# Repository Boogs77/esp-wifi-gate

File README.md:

# esp-wifi-gate
ESP circuit for Wifi Came gate control

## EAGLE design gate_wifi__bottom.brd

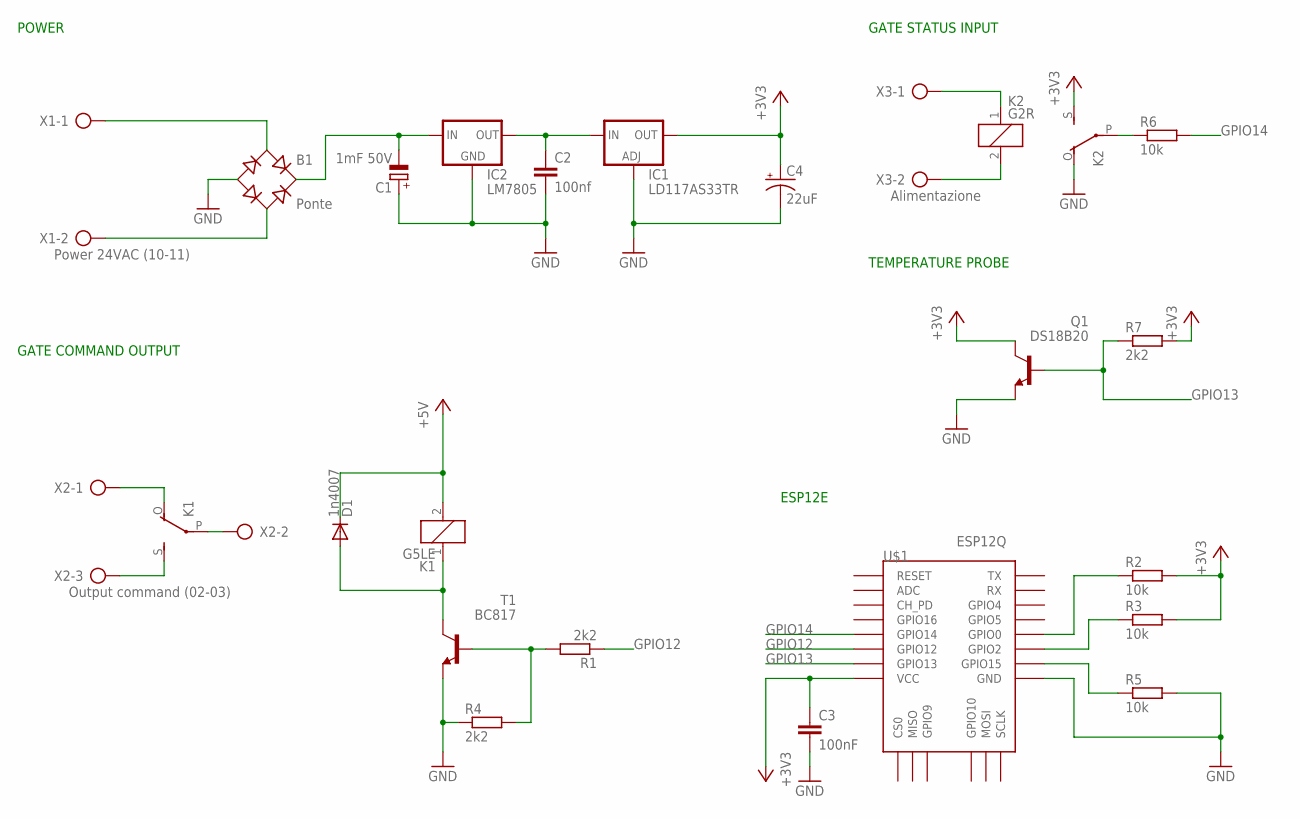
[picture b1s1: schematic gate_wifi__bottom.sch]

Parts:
B1: Ponte; RB1A_MOD
C1: 1mF 50V; E5-8,5
C2: 100nf; C0805K
C3: 100nF; C0805K
C4: 22uF; E2,5-5
D1: 1n4007; DO-214AC
IC1: LD117AS33TR; SOT223
IC2: LM7805; 78XXS
K1: G5LE
K2: G2R
Q1: DS18B20; TO92
R1, R4, R7: 2k2; M0805
R2, R3, R5, R6: 10k; M0805
T1: BC817; SOT23-BEC
U$1: ESP12Q
X1: Power 24VAC (10-11); AK500/2
X2: Output command (02-03); AK500/3
X3: Alimentazione; AK500/2

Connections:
+3V3: C3.1, C4.+, IC1.4 (OUT), K2.S, Q1.1 (C), R2.2, R3.2, R7.2, U$1.VCC
+5V: D1.C, K1.2
GND: B1.-, C1.+, C2.2, C3.2, C4.-, IC1.1 (ADJ), IC2.GND, K2.O, Q1.3 (E), R4.1, R5.2, T1.E, U$1.GND
GPIO12: R1.1, U$1.GPIO12
GPIO13: Q1.2 (B), R7.1, U$1.GPIO13
GPIO14: R6.2, U$1.GPIO14
unnamed: B1.AC1, X1.1
unnamed: B1.AC2, X1.2
unnamed: K1.P, X2.2
unnamed: K1.S, X2.3
unnamed: K1.O, X2.1
unnamed: D1.A, K1.1, T1.C
unnamed: R5.1, U$1.GPIO15
unnamed: R1.2, R4.2, T1.B
unnamed: B1.+, C1.-, IC2.IN
unnamed: K2.1, X3.1
unnamed: C2.1, IC1.3 (IN), IC2.OUT
unnamed: K2.2, X3.2
unnamed: R3.1, U$1.GPIO2
unnamed: R2.1, U$1.GPIO0
unnamed: K2.P, R6.1

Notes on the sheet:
POWER
GATE COMMAND OUTPUT
GATE STATUS INPUT
TEMPERATURE PROBE
ESP12E

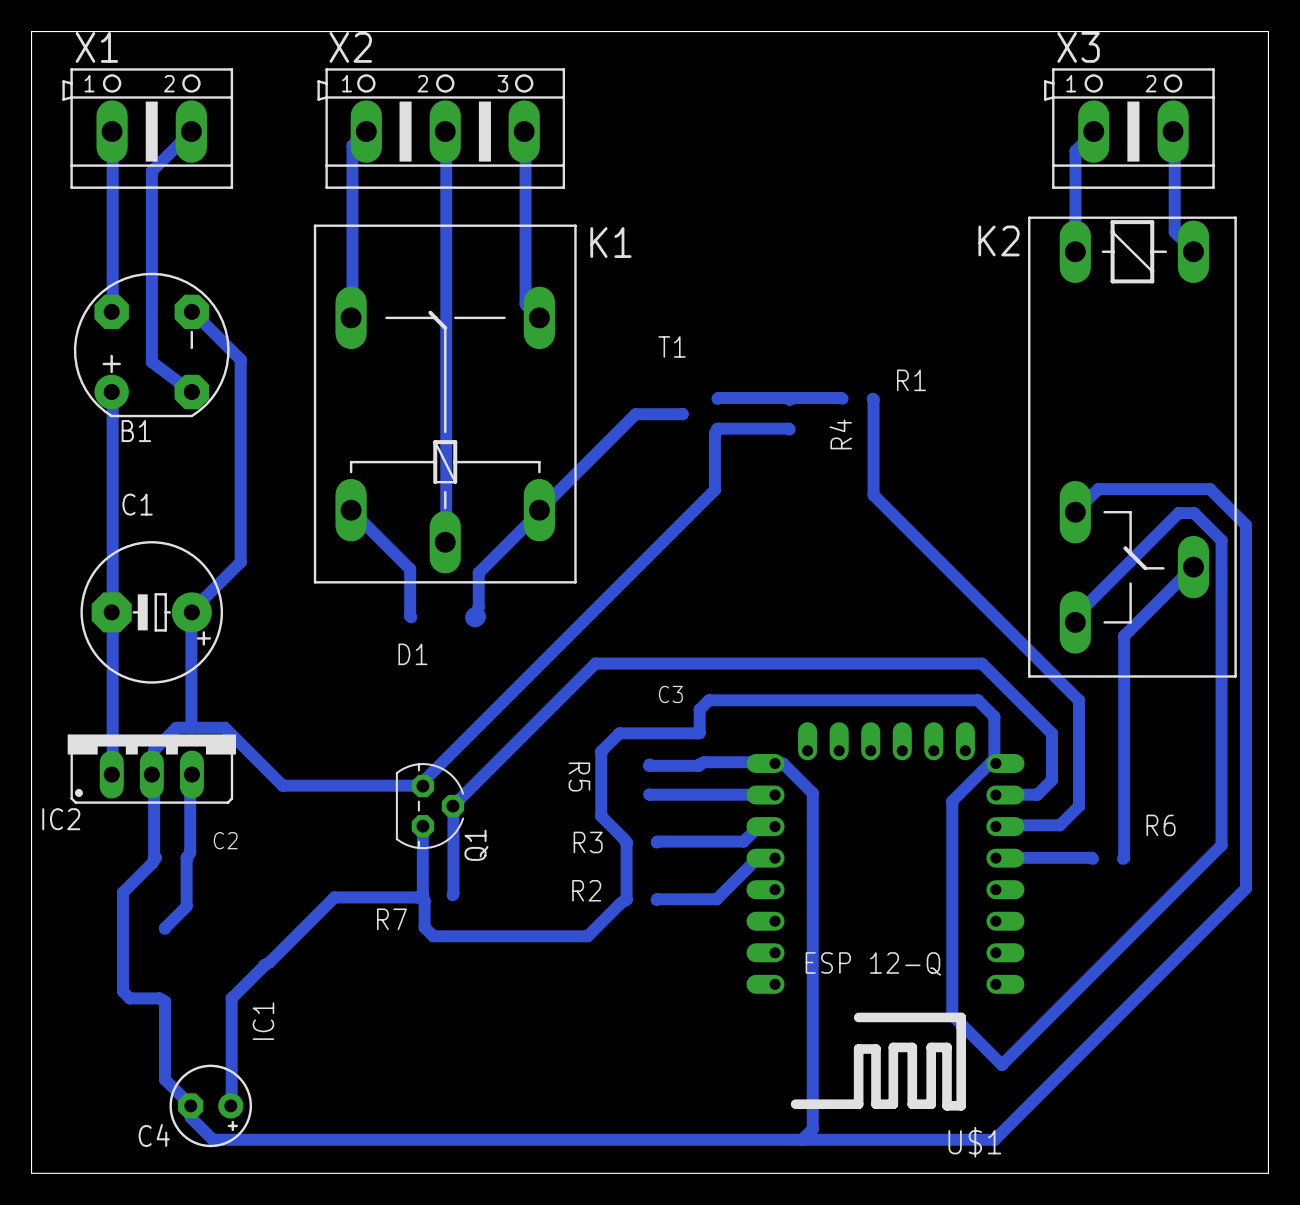
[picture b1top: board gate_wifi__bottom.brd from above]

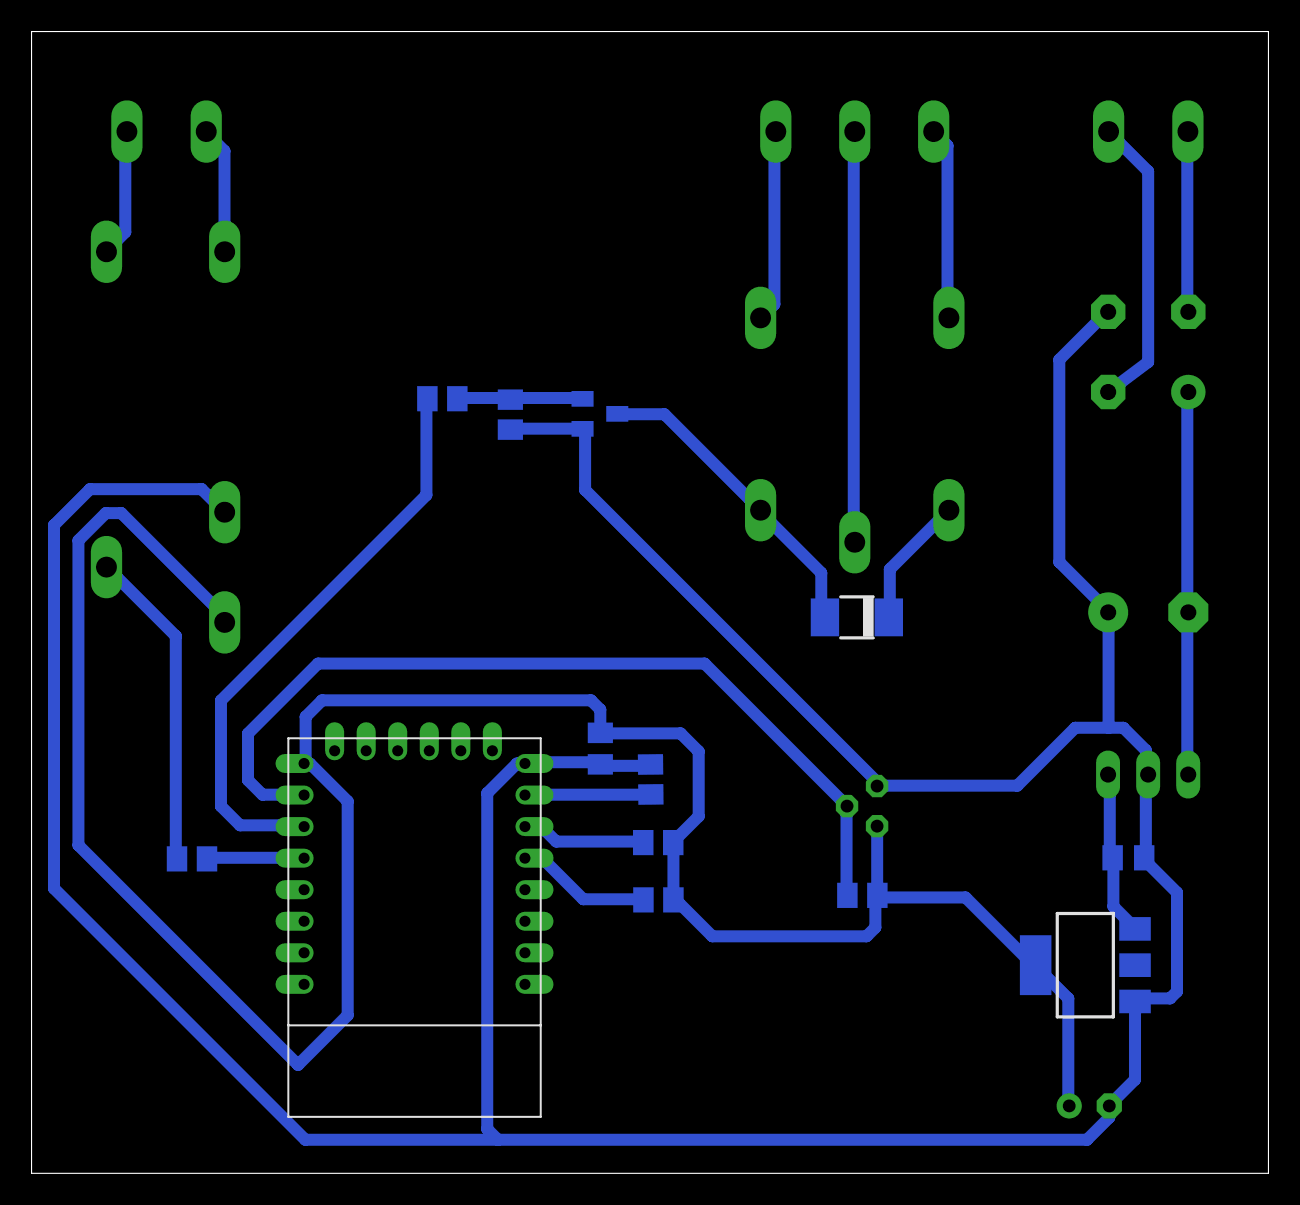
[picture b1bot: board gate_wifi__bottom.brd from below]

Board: 2 copper layers, 78.4 x 72.4 mm, 23 parts (12 on the bottom side), 21 nets.
